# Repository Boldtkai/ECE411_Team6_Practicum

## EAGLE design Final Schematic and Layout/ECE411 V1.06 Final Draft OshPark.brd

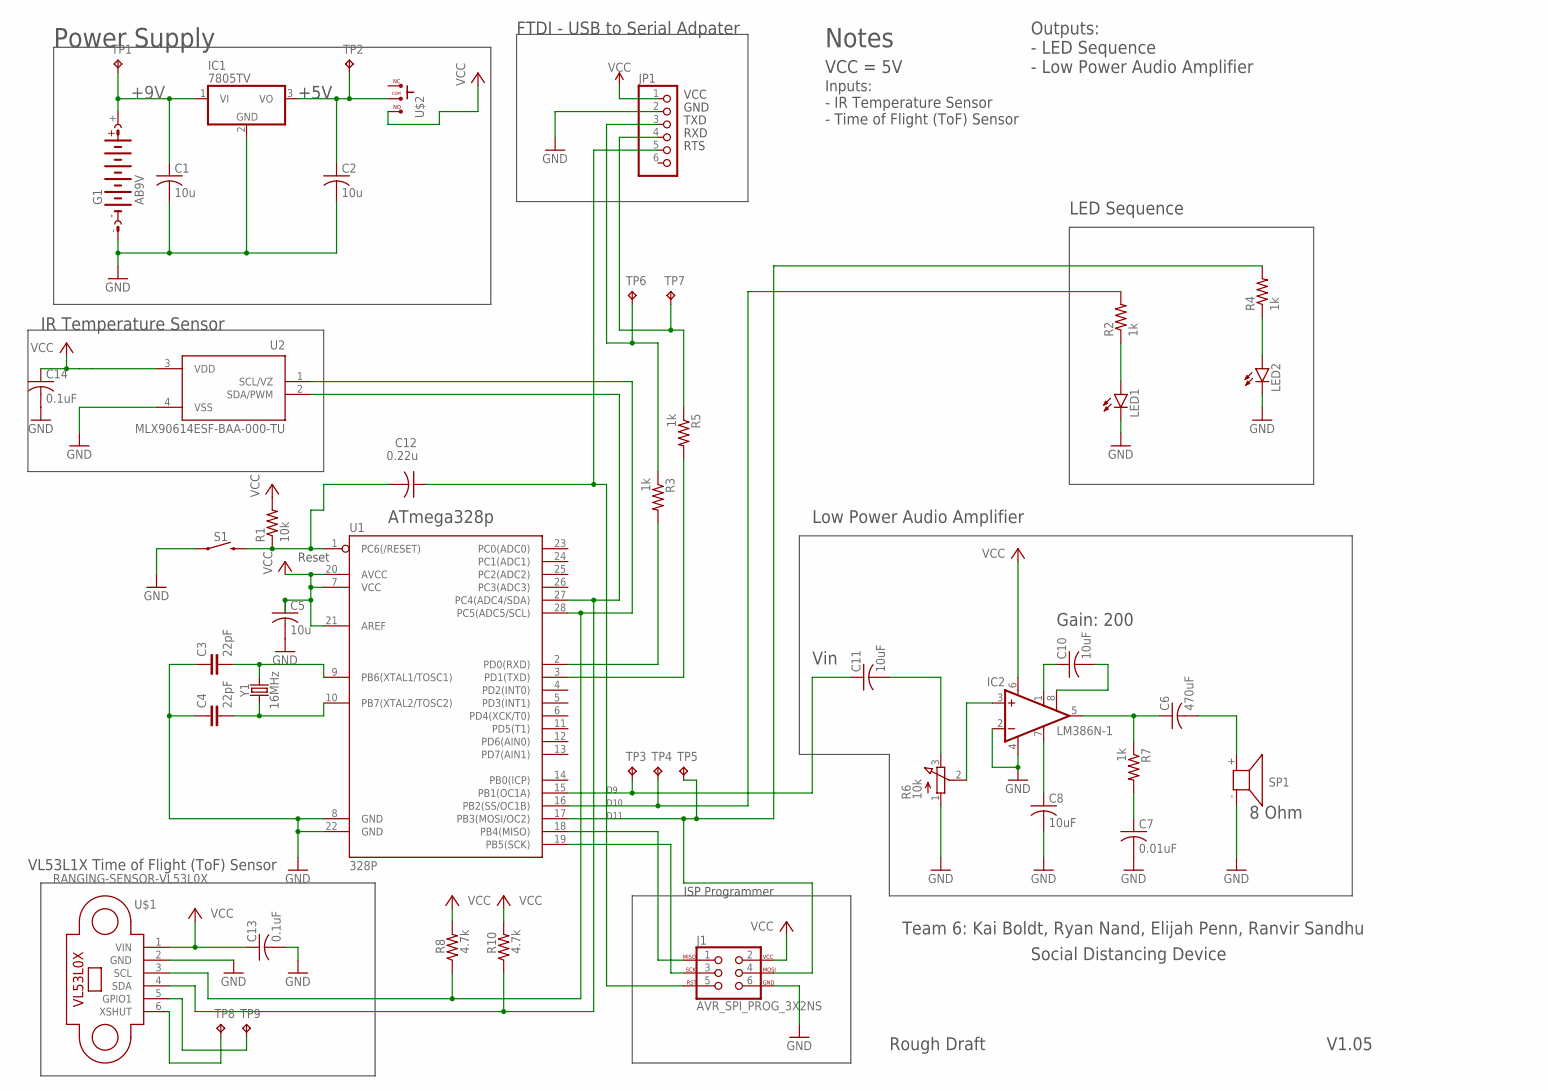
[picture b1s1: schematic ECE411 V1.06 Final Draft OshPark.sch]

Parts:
C1, C2, C5: 10u; C025-024X044
C3, C4: 22pF; CAP-PTH-2.54
C6: 470uF; C050-024X044
C7: 0.01uF; C025-024X044
C8, C10, C11: 10uF; C025-024X044
C12: 0.22u; C050-030X075
C13, C14: 0.1uF; C025-024X044
G1: AB9V
IC1: 7805TV; TO220V
IC2: LM386N-1; DIL08
J1: AVR_SPI_PROG_3X2NS; 2X3-NS
JP1: PINHD-1X6; 1X06
LED1, LED2: LED3MM
R1: 10k; 0204/7
R2, R4: 1k; 0204/5
R3, R5, R7: 1k; 0204/7
R6: 10k; 3RP/1610N
R8, R10: 4.7k; 0204/7
S1: MOMENTARY-SWITCH-SPST-PTH-6.0MM; TACTILE_SWITCH_PTH_6.0MM
SP1: KSS1201
TP1, TP2, TP3, TP4, TP5, TP6, TP7, TP8, TP9: TPPAD1-13; P1-13
U1: 328P; DIP28
U2: MLX90614ESF-BAA-000-TU; TO254P942H425-4
U$1: RANGING-SENSOR-VL53L0X
U$2: -SLIDERS; CON3
Y1: 16MHz; HC49US

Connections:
5V: C2.1, IC1.3 (VO), TP2.TP, U$2.P$2 (2)
+9V: C1.1, G1.+, IC1.1 (VI), TP1.TP
AUDIO: C11.1, TP3.TP, U1.15 (PB1(OC1A))
BYPASS: C8.1, IC2.7 (BYPASS)
GAIN: C10.1, IC2.1 (GAIN)
GND: C1.2, C2.2, C3.1, C4.1, C5.2, C7.2, C8.2, C13.2, C14.2, G1.-, IC1.2 (GND), IC2.2 (-IN), IC2.4 (GND), J1.6, JP1.2, LED1.K (C), LED2.K (C), R6.1 (A), S1.1, SP1.- (2), U1.8 (GND), U1.22 (GND), U2.4 (VSS), U$1.2 (GND)
GPIO1: TP9.TP, U$1.5 (GPIO1)
INPUT: IC2.3 (+IN), R6.2 (S)
LED1: R2.2, TP4.TP, U1.16 (PB2(SS/OC1B))
LED2: J1.4, R4.2, TP5.TP, U1.17 (PB3(MOSI/OC2))
unnamed: C3.2, U1.9 (PB6(XTAL1/TOSC1)), Y1.2
unnamed: J1.1, U1.18 (PB4(MISO))
unnamed: C4.2, U1.10 (PB7(XTAL2/TOSC2)), Y1.1
unnamed: TP8.TP, U$1.6 (XSHUT)
unnamed: J1.3, U1.19 (PB5(SCK))
unnamed: C7.1, R7.2
unnamed: C10.2, IC2.8 (GAIN)
unnamed: C11.2, R6.3 (E)
unnamed: LED1.A, R2.1
unnamed: LED2.A, R4.1
RESET: C12.2, R1.1, S1.3 (2), U1.1 (PC6(/RESET))
RTS: C12.1, J1.5, JP1.5
RXD: JP1.4, R5.1, R5.2, TP7.TP, U1.3 (PD1(TXD))
SCL: R8.1, U1.28 (PC5(ADC5/SCL)), U2.1 (SCL/VZ), U$1.3 (SCL)
SDA: R10.1, U1.27 (PC4(ADC4/SDA)), U2.2 (SDA/PWM), U$1.4 (SDA)
TXD: JP1.3, R3.1, R3.2, TP6.TP, U1.2 (PD0(RXD))
VCC: C5.1, C13.1, C14.1, IC2.6 (VS), J1.2, JP1.1, R1.2, R8.2, R10.2, U1.7 (VCC), U1.20 (AVCC), U1.21 (AREF), U2.3 (VDD), U$1.1 (VIN), U$2.P$3 (3)
VO: C6.2, SP1.+ (1)
VOUT: C6.1, IC2.5 (OUT), R7.1

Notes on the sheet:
+5V
Power Supply
IR Temperature Sensor
Low Power Audio Amplifier
LED Sequence
Team 6: Kai Boldt, Ryan Nand, Elijah Penn, Ranvir Sandhu
Gain: 200
ATmega328p
Social Distancing Device
Notes
VCC = 5V
Outputs: - LED Sequence - Low Power Audio Amplifier
Vin
8 Ohm
VCC
GND
TXD
RXD
RTS
FTDI - USB to Serial Adpater
Rough Draft
Reset
V1.05
VL53L1X Time of Flight (ToF) Sensor
Inputs: - IR Temperature Sensor - Time of Flight (ToF) Sensor
D10
D11
ISP Programmer

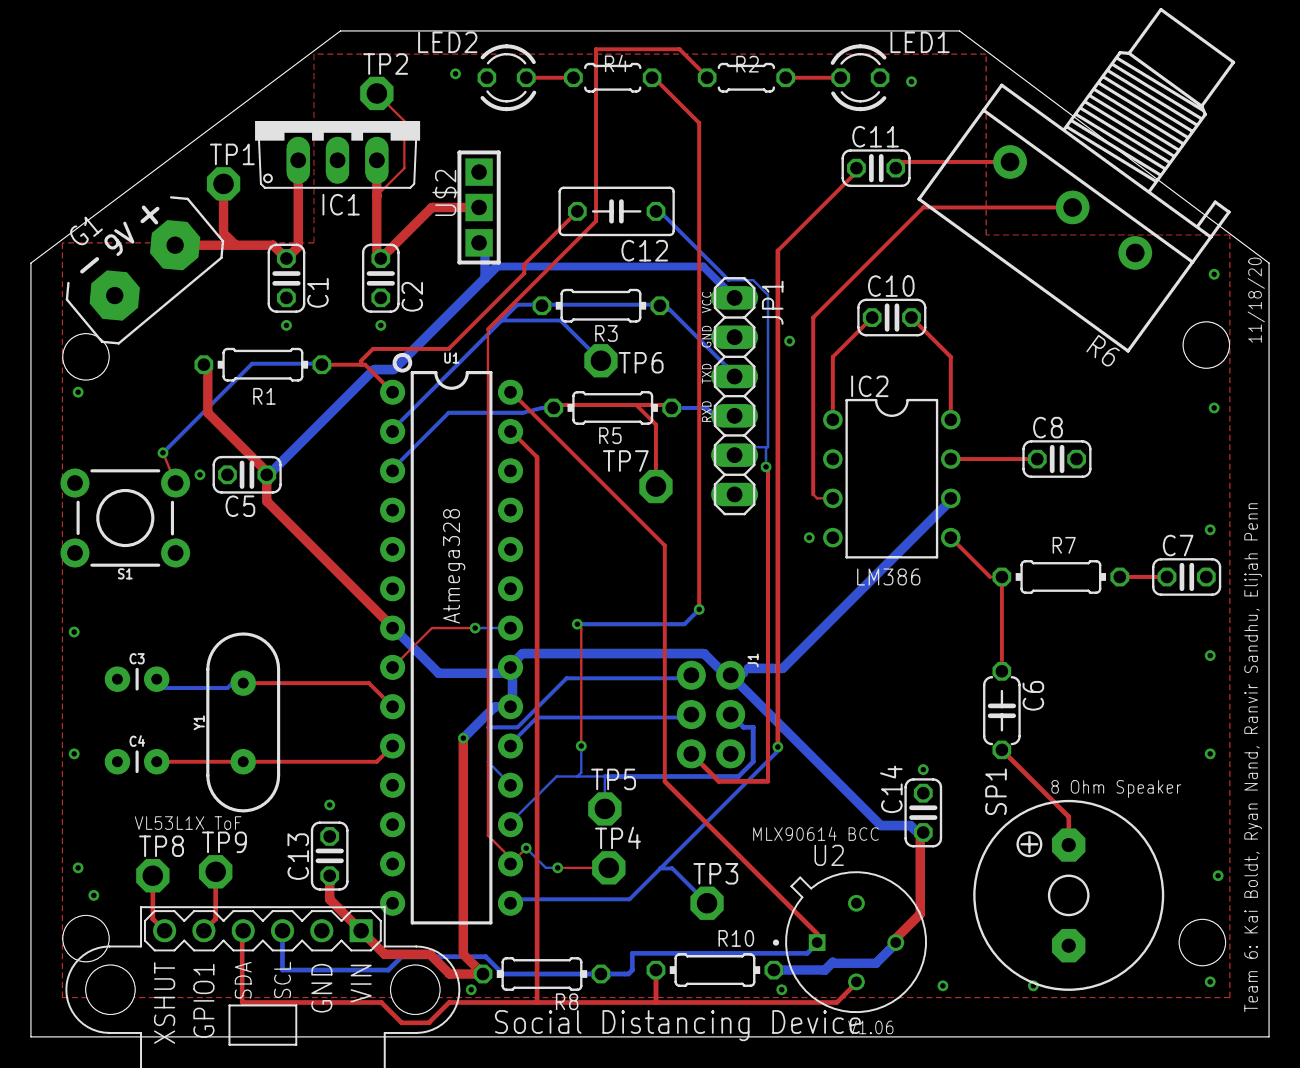
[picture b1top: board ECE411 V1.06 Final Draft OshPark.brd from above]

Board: 2 copper layers, 80.0 x 65.0 mm, 45 parts (0 on the bottom side), 29 nets.

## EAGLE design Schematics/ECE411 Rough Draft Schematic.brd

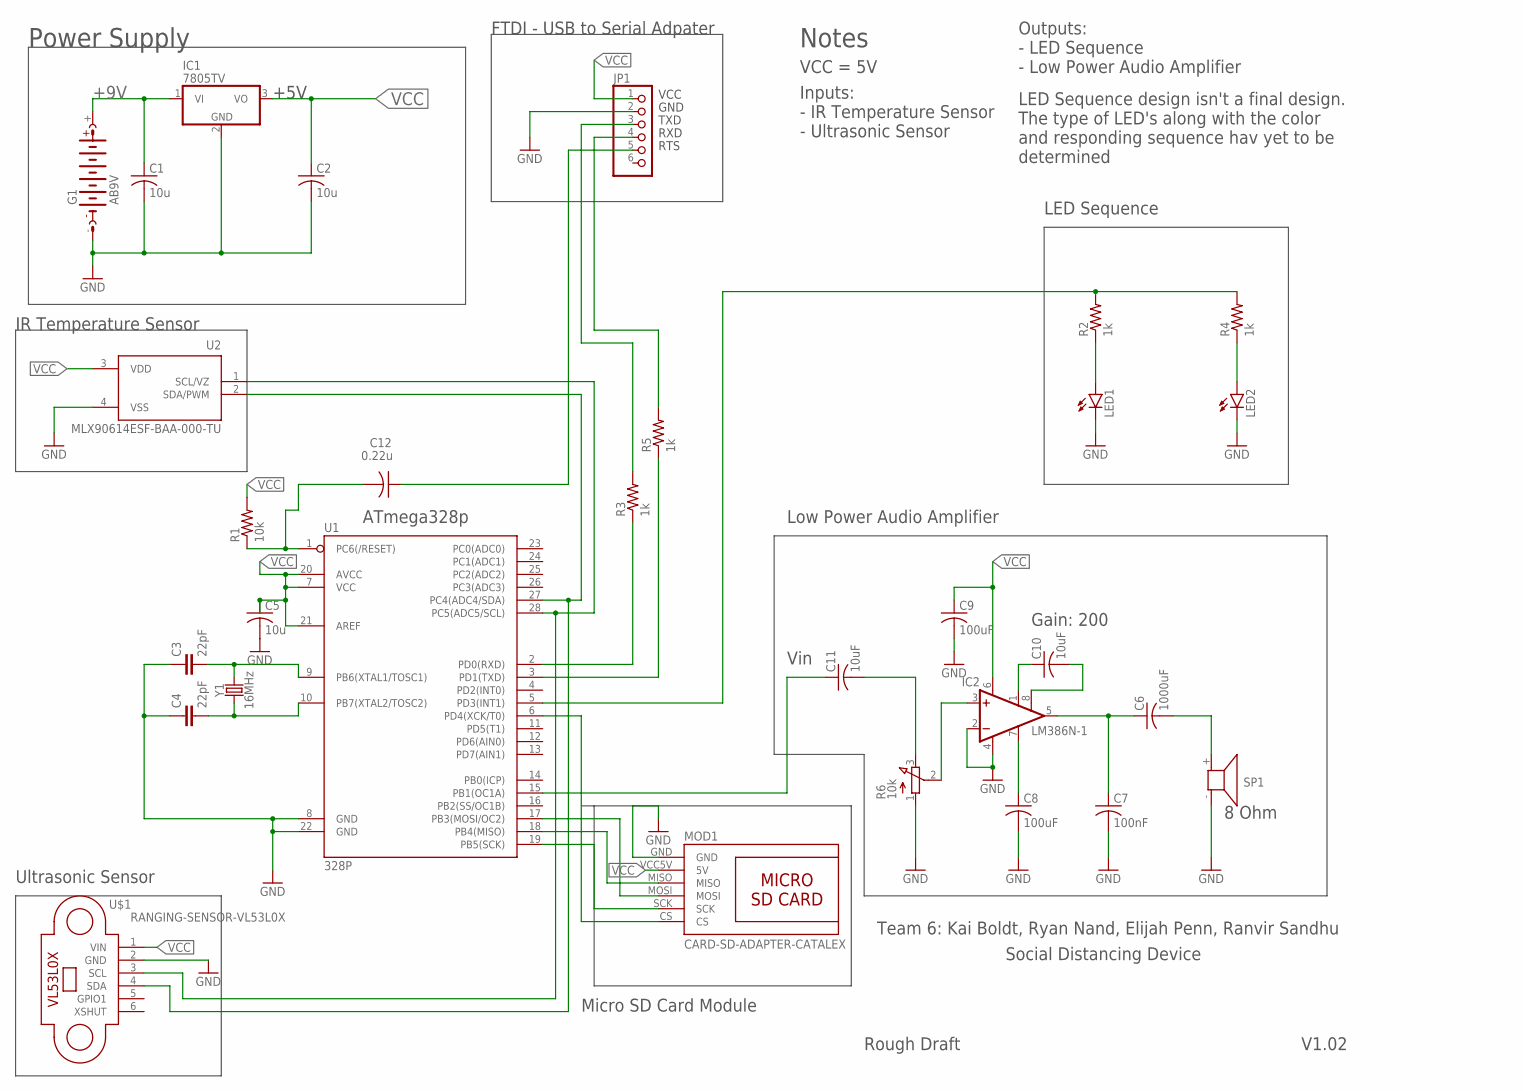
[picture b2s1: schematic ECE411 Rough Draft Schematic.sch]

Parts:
C1, C2, C5: 10u; C025-024X044
C3, C4: 22pF; CAP-PTH-2.54
C6: 1000uF; C025-024X044
C7: 100nF; C025-024X044
C8, C9: 100uF; C025-024X044
C10, C11: 10uF; C025-024X044
C12: 0.22u; C050-030X075
G1: AB9V
IC1: 7805TV; TO220V
IC2: LM386N-1; DIL08
JP1: PINHD-1X6; 1X06
LED1, LED2: LED3MM
MOD1: CARD-SD-ADAPTER-CATALEX
R1: 10k; 0204/7
R2, R3, R4, R5: 1k; 0204/5
R6: 10k; 3RP/1610N
SP1: KSS1201
U1: 328P; DIP28
U2: MLX90614ESF-BAA-000-TU; TO254P942H425-4
U$1: RANGING-SENSOR-VL53L0X
Y1: 16MHz; HC49US

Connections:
+9V: C1.1, G1.+, IC1.1 (VI)
CS: MOD1.CS, U1.6 (PD4(XCK/T0))
GND: C1.2, C2.2, C3.1, C4.1, C5.2, C7.2, C8.2, C9.2, G1.-, IC1.2 (GND), IC2.2 (-IN), IC2.4 (GND), JP1.2, LED1.K (C), LED2.K (C), MOD1.GND, R6.1 (A), SP1.- (2), U1.8 (GND), U1.22 (GND), U2.4 (VSS), U$1.2 (GND)
MISO: MOD1.MISO, U1.18 (PB4(MISO))
MOSI: MOD1.MOSI, U1.17 (PB3(MOSI/OC2))
unnamed: C3.2, U1.9 (PB6(XTAL1/TOSC1)), Y1.2
unnamed: C12.2, R1.1, U1.1 (PC6(/RESET))
unnamed: C4.2, U1.10 (PB7(XTAL2/TOSC2)), Y1.1
unnamed: C8.1, IC2.7 (BYPASS)
unnamed: C6.1, C7.1, IC2.5 (OUT)
unnamed: C10.2, IC2.8 (GAIN)
unnamed: IC2.3 (+IN), R6.2 (S)
unnamed: C10.1, IC2.1 (GAIN)
unnamed: C11.2, R6.3 (E)
unnamed: C11.1, U1.15 (PB1(OC1A))
unnamed: R2.2, R4.2, U1.5 (PD3(INT1))
unnamed: LED1.A, R2.1
unnamed: LED2.A, R4.1
unnamed: R3.1, U1.2 (PD0(RXD))
RTS: C12.1, JP1.5
RXD: JP1.4, R5.1, R5.2, U1.3 (PD1(TXD))
SCK: MOD1.SCK, U1.19 (PB5(SCK))
SCL: U1.28 (PC5(ADC5/SCL)), U2.1 (SCL/VZ), U$1.3 (SCL)
SDA: U1.27 (PC4(ADC4/SDA)), U2.2 (SDA/PWM), U$1.4 (SDA)
TXD: JP1.3, R3.2
VCC: C2.1, C5.1, C9.1, IC1.3 (VO), IC2.6 (VS), JP1.1, MOD1.VCC5V (5V), R1.2, U1.7 (VCC), U1.20 (AVCC), U1.21 (AREF), U2.3 (VDD), U$1.1 (VIN)
VO: C6.2, SP1.+ (1)

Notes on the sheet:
+5V
Power Supply
IR Temperature Sensor
Low Power Audio Amplifier
LED Sequence
Micro SD Card Module
Ultrasonic Sensor
Team 6: Kai Boldt, Ryan Nand, Elijah Penn, Ranvir Sandhu
Gain: 200
ATmega328p
Social Distancing Device
Notes
Inputs: - IR Temperature Sensor - Ultrasonic Sensor
VCC = 5V
Outputs: - LED Sequence - Low Power Audio Amplifier
LED Sequence design isn't a final design. The type of LED's along with the color and responding sequence hav yet to be determined
Vin
8 Ohm
VCC
GND
TXD
RXD
RTS
FTDI - USB to Serial Adpater
V1.02
Rough Draft

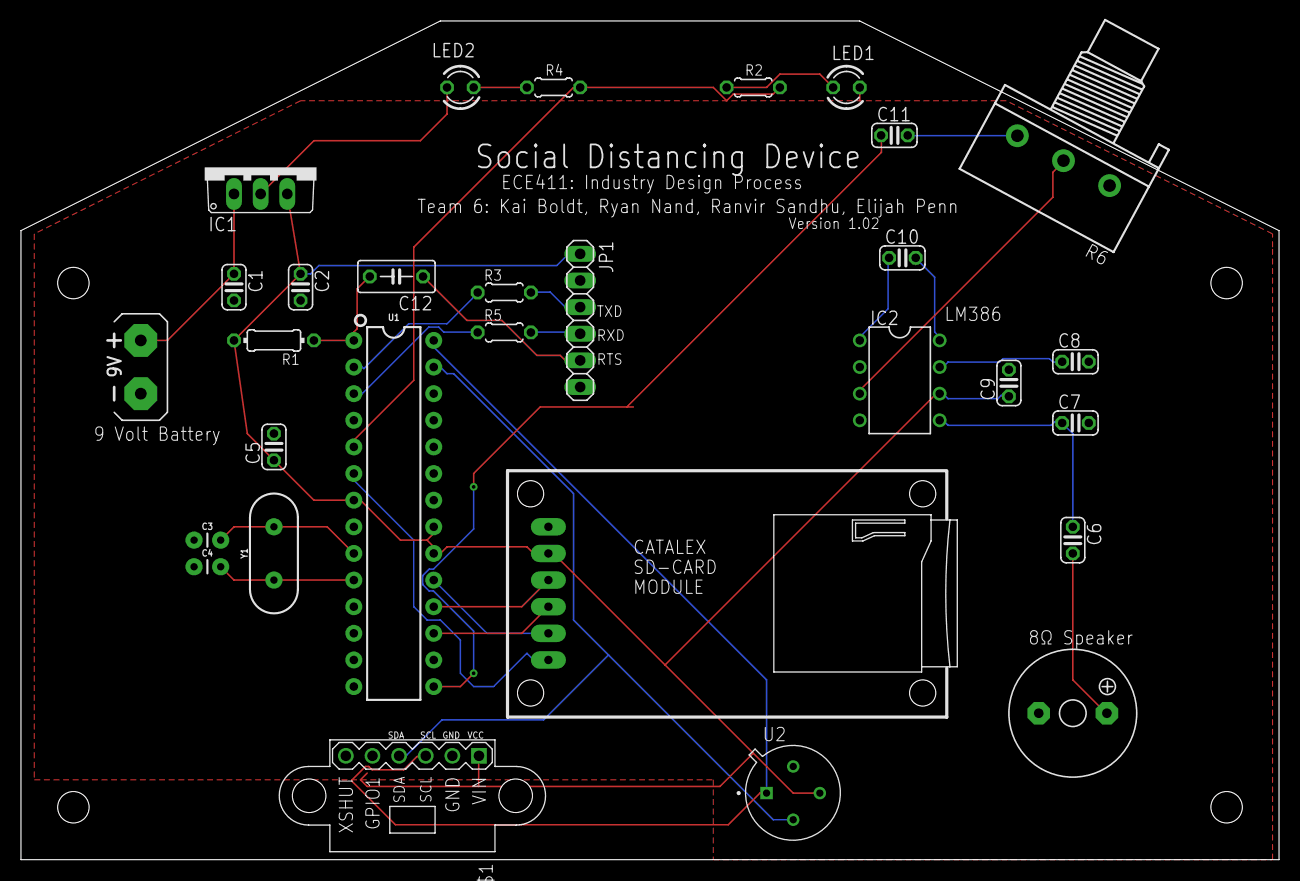
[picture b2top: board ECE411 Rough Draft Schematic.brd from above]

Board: 2 copper layers, 120.0 x 80.0 mm, 30 parts (0 on the bottom side), 27 nets.

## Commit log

2020-10-14 Create LICENSE
2020-10-14 License created
2020-10-15 Update LICENSE
2020-10-15 Create Project Ideas
2020-11-01 Add files via upload
    ESP32 and TOF sensor Datasheets
2020-11-02 Create Preliminary Schematics
2020-11-02 Delete Audio Amplifier - SD Card Module.HEIC
    Wrong Format
2020-11-02 Delete Input Sensors.HEIC
    Wrong Format
2020-11-02 Delete ECE411 Preliminary Schematic V1.01.png
    Has been updated
2020-11-02 Delete Audio_Amplifier_-_SD_Card_Module.jpg
    Needed to resize
2020-11-04 SMT voltage regulator for 5V to 3.3V
2020-11-12 Create Bill of Materials
2020-11-12 Create Bill of Materials (BoM)
2020-11-14 Create Project Schedule
2020-11-18 Create Final Draft of Schematic and Layout
2020-11-19 Create Peer Design Review
2020-11-21 Create Detail Design
2020-12-05 Create readme
    Placeholder text
2020-12-05 Enclosure files for project
2020-12-05 Pictures of enclosure in Fusion 360
2020-12-06 3D Printed Parts
2020-12-07 Improvements/Fixes to Enclosure
2020-12-08 Create Demonstration Video
2020-12-08 Create Test Plan
2020-12-09 Extra Pictures of 3D Printed Enclosure
2020-12-09 Actual PCB
2020-12-09 Create Program Code
2020-12-09 Update Program Code

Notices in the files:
parts and their libraries:
SparkFun-Capacitors: Licensing: Creative Commons ShareAlike 4.0 International - https://creativecommons.org/licenses/by-sa/4.0
VL53L0X: Released under the Creative Commons Attribution 4.0 International License: http://creativecommons.org/licenses/by/4.0
